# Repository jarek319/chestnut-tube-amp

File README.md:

# chestnut-tube-amp
Tube Amplifier using a really interesting-looking tube

The 832A is a really awesome looking vacuum tube.

I wish I could figure out how to make it sing.

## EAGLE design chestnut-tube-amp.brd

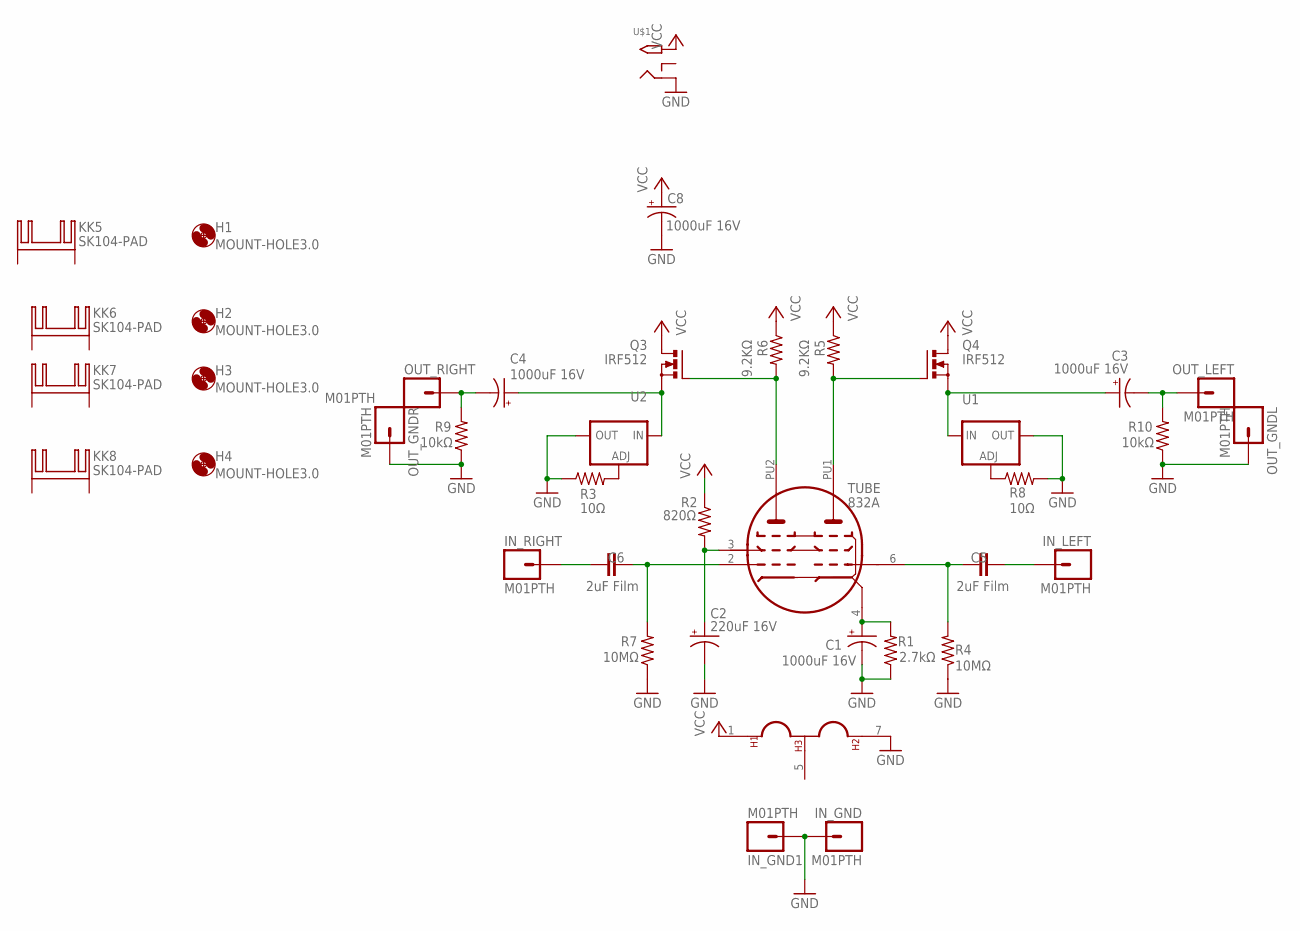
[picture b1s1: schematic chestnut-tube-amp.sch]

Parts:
C1, C3, C4, C8: 1000uF 16V; E5-10,5
C2: 220uF 16V; E2,5-7
C5, C6: 2uF Film; C375-155X418
H1, H2, H3, H4: MOUNT-HOLE3.0; 3,0
IN_GND, IN_GND1: M01PTH; 1X01
IN_LEFT: M01PTH; 1X01
IN_RIGHT: M01PTH; 1X01
KK5, KK6, KK7, KK8: SK104-PAD
OUT_GNDL: M01PTH; 1X01
OUT_GNDR: M01PTH; 1X01
OUT_LEFT: M01PTH; 1X01
OUT_RIGHT: M01PTH; 1X01
Q3, Q4: IRF512; TO220BV
R1: 2.7kΩ; 0207/7
R2: 820Ω; 0207/7
R3, R8: 10Ω; 0207/7
R4, R7: 10MΩ; 0207/7
R5, R6: 9.2KΩ; 0207/7
R9, R10: 10kΩ; 0207/7
TUBE: 832A
U1, U2: LM317TS; 317TS
U$1: 2.1MMJACKTHM; PJ-102A

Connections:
GND: C1.-, C2.-, C8.-, IN_GND.1, IN_GND1.1, OUT_GNDL.1, OUT_GNDR.1, R1.1, R3.1, R4.1, R7.1, R8.2, R9.1, R10.1, TUBE.7, U1.2 (OUT), U2.2 (OUT), U$1.RING
unnamed: C2.+, R2.2, TUBE.3
unnamed: Q3.G, R6.2, TUBE.PU2
unnamed: C6.2, R7.2, TUBE.2
unnamed: C5.2, R4.2, TUBE.6
unnamed: R3.2, U2.1 (ADJ)
unnamed: Q4.G, R5.2, TUBE.PU1
unnamed: C5.1, IN_LEFT.1
unnamed: C1.+, R1.2, TUBE.4
unnamed: C4.+, Q3.S, U2.3 (IN)
unnamed: C3.+, Q4.S, U1.3 (IN)
unnamed: R8.1, U1.1 (ADJ)
unnamed: C6.1, IN_RIGHT.1
unnamed: C3.-, OUT_LEFT.1, R10.2
unnamed: C4.-, OUT_RIGHT.1, R9.2
VCC: C8.+, Q3.D, Q4.D, R2.1, R5.1, R6.1, TUBE.1, U$1.TIP

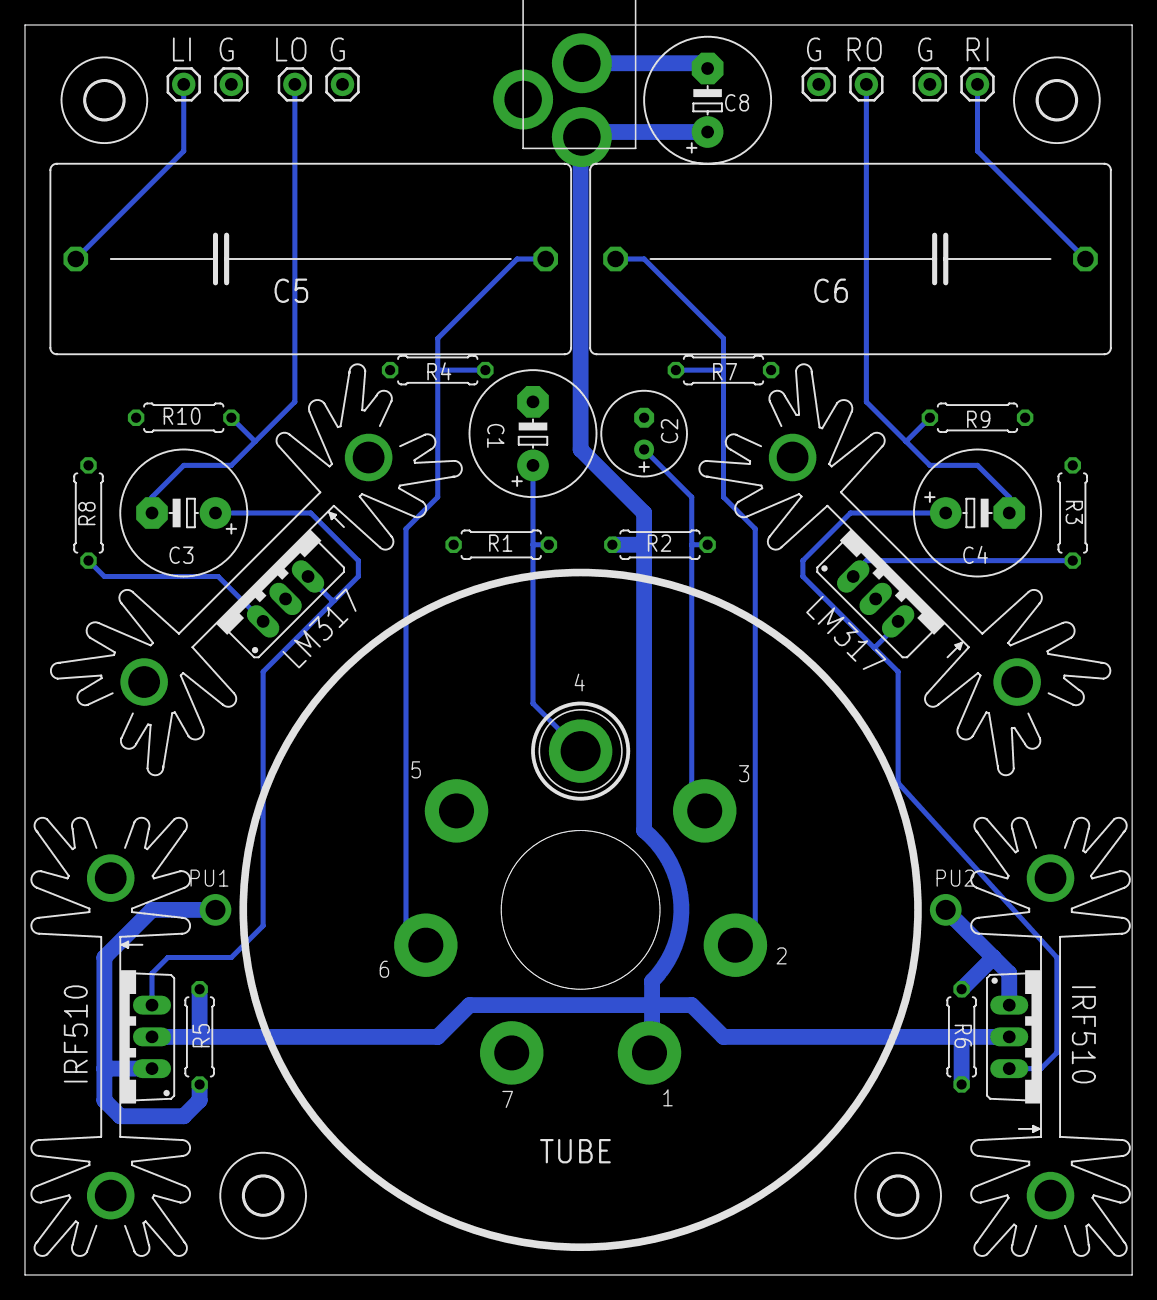
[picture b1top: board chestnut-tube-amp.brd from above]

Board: 2 copper layers, 88.6 x 100.0 mm, 39 parts (0 on the bottom side), 16 nets.

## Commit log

2018-07-04 design tested: nonworking

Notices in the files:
parts and their libraries:
SparkFun-Connectors: Licensing: CC v3.0 Share-Alike You are welcome to use this library for commercial purposes.
